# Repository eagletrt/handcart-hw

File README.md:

# Handcart

Battery charger controller board.

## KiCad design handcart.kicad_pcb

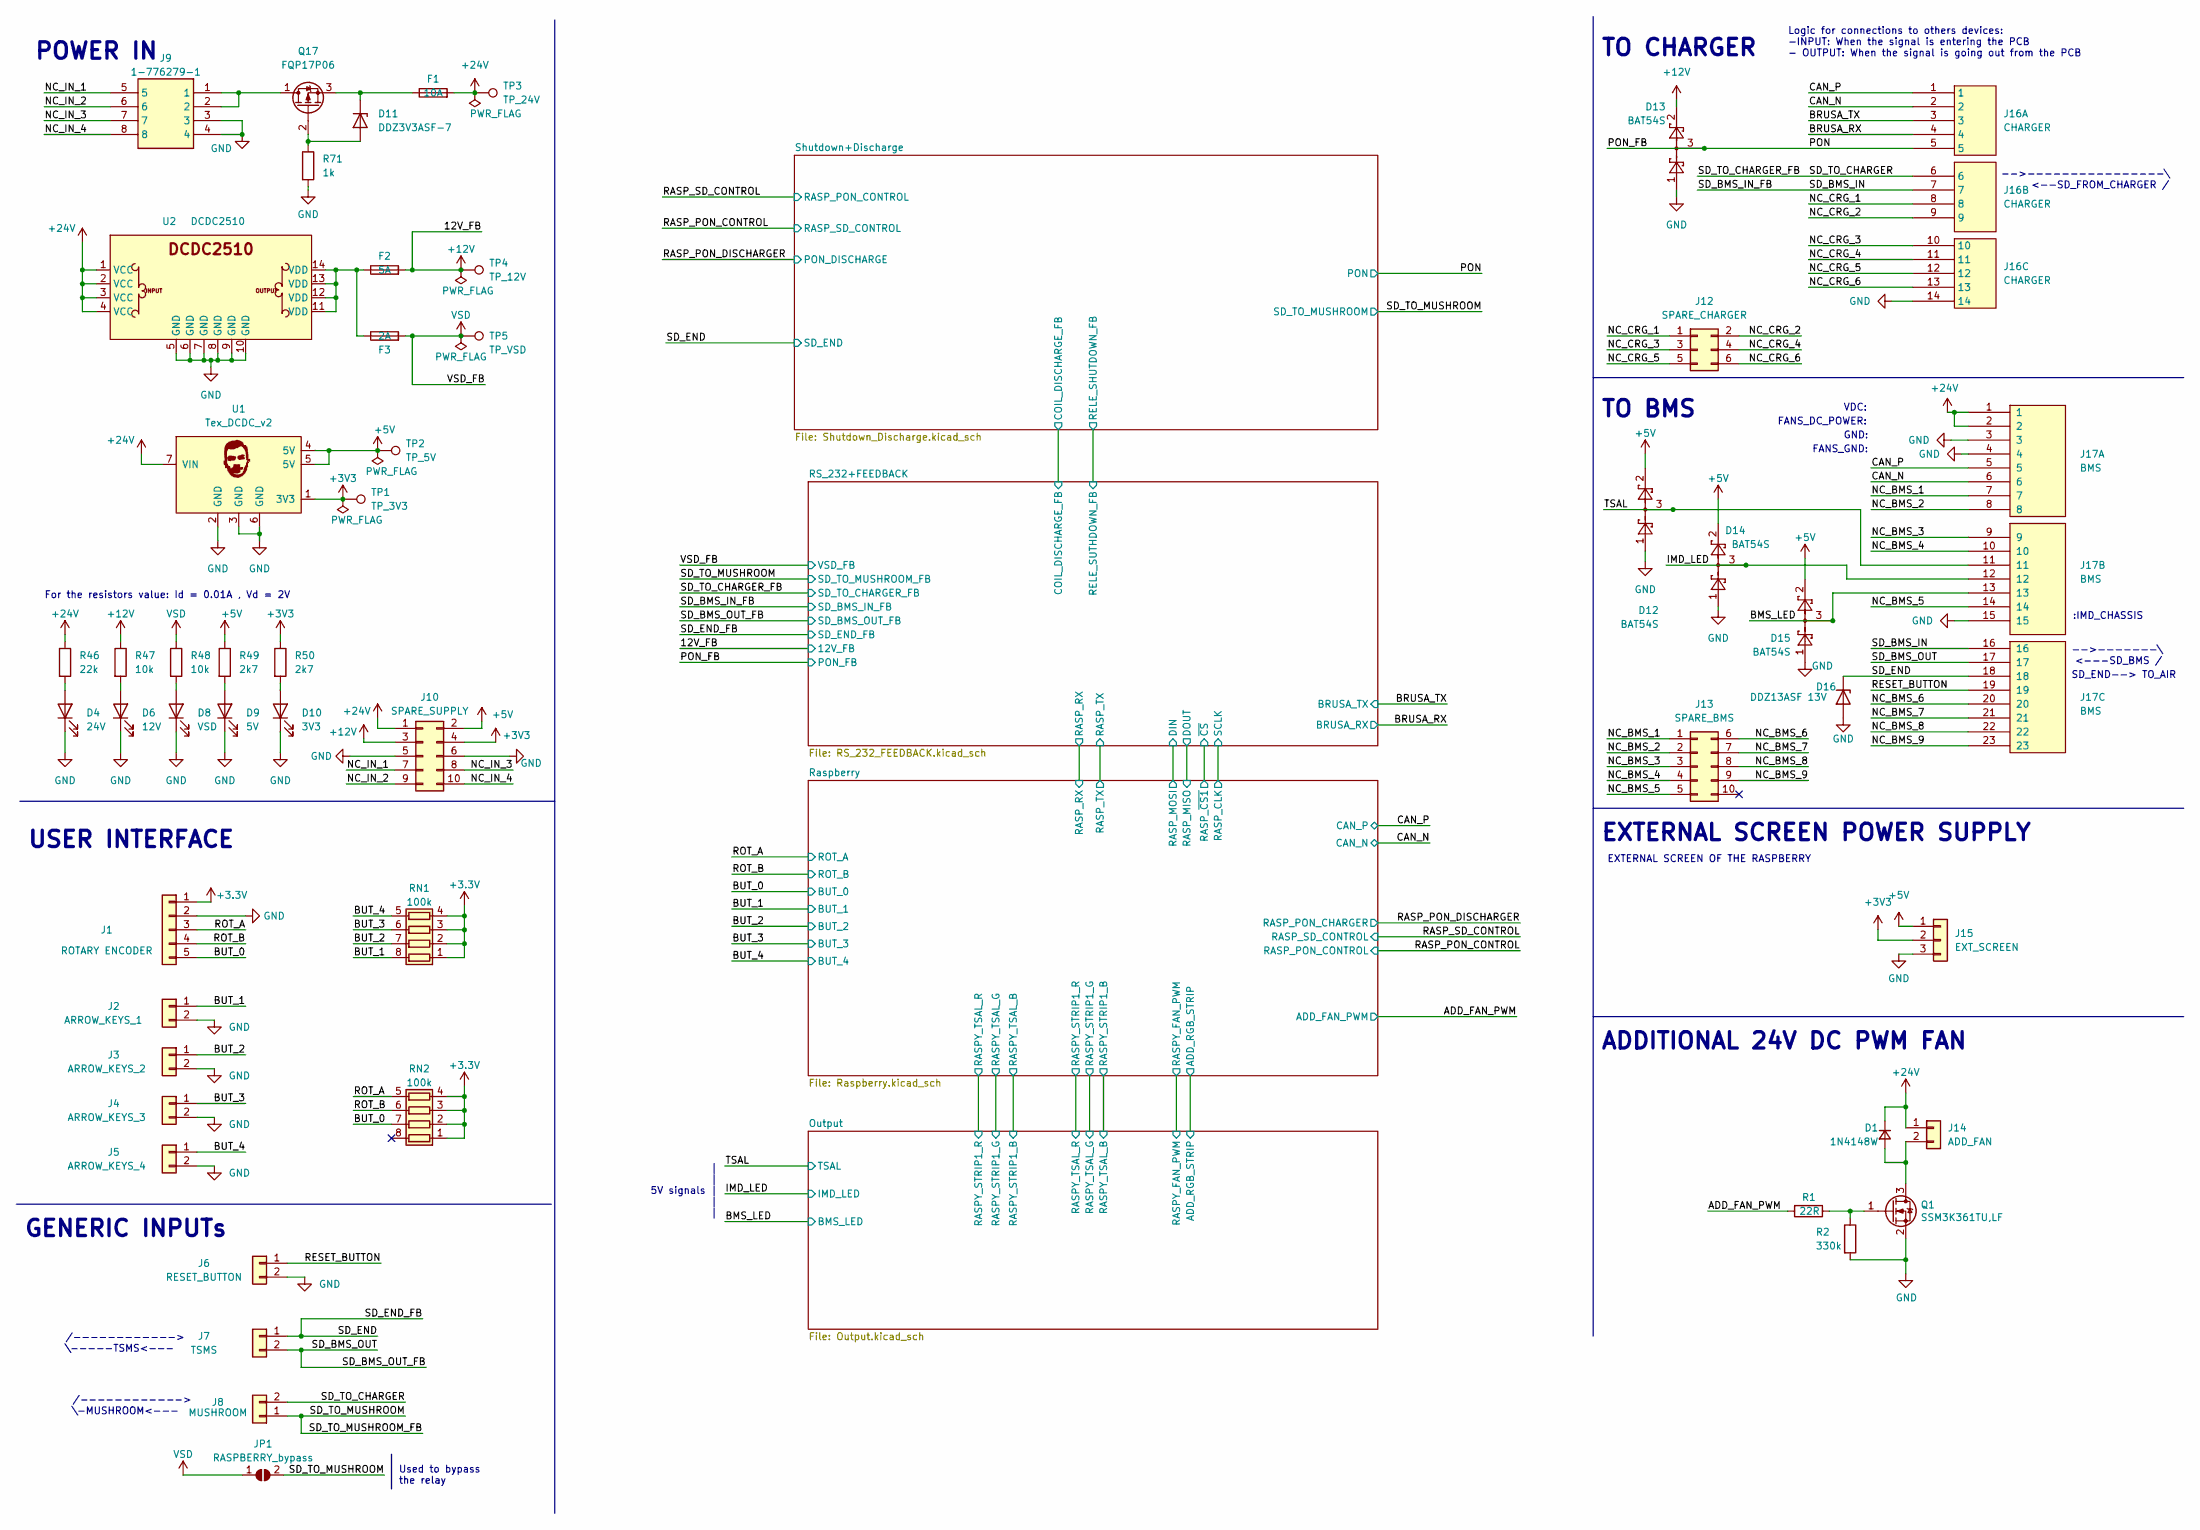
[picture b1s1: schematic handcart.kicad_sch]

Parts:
D1: 1N4148W; D_SOD-323_HandSoldering
D4: 24V; R_0805_2012Metric
D6: 12V; R_0805_2012Metric
D8: VSD; R_0805_2012Metric
D9: 5V; R_0805_2012Metric
D10: 3V3; R_0805_2012Metric
D11: DDZ3V3ASF-7; D_SOD-323
D12, D13, D14, D15: BAT54S; SOT-23
D16: DDZ13ASF 13V; D_SOD-323F
F1: 10A; Keystone-Fuseholder 3557-2
F2: 5A; Keystone-Fuseholder 3557-2
F3: 2A; Keystone-Fuseholder 3557-2
J1: ROTARY ENCODER; Molex_Micro-Fit_3.0_43650-0515_1x05_P3.00mm_Vertical
J2: ARROW_KEYS_1; Molex_Micro-Fit_3.0_43650-0215_1x02_P3.00mm_Vertical
J3: ARROW_KEYS_2; Molex_Micro-Fit_3.0_43650-0215_1x02_P3.00mm_Vertical
J4: ARROW_KEYS_3; Molex_Micro-Fit_3.0_43650-0215_1x02_P3.00mm_Vertical
J5: ARROW_KEYS_4; Molex_Micro-Fit_3.0_43650-0215_1x02_P3.00mm_Vertical
J6: RESET_BUTTON; Molex_Micro-Fit_3.0_43650-0215_1x02_P3.00mm_Vertical
J7: TSMS; Molex_Micro-Fit_3.0_43650-0215_1x02_P3.00mm_Vertical
J8: MUSHROOM; Molex_Micro-Fit_3.0_43650-0215_1x02_P3.00mm_Vertical
J9: 1-776279-1; 17762791; Mouser Part Number 571-1-776279-1
J10: SPARE_SUPPLY; Molex_Micro-Fit_3.0_43045-1012_2x05_P3.00mm_Vertical
J12: SPARE_CHARGER; Molex_Micro-Fit_3.0_43045-0612_2x03_P3.00mm_Vertical
J13: SPARE_BMS; Molex_Micro-Fit_3.0_43045-1012_2x05_P3.00mm_Vertical
J14: ADD_FAN; Molex_Micro-Fit_3.0_43650-0215_1x02_P3.00mm_Vertical
J15: EXT_SCREEN; Molex_Micro-Fit_3.0_43650-0315_1x03_P3.00mm_Vertical
J16: CHARGER; TE_776266-4
J17: BMS; TE_776087-4
JP1: RASPBERRY_bypass; SolderJumper-2_P1.3mm_Open_Pad1.0x1.5mm
Q1: SSM3K361TU,LF; SOTFL65P210X75-3N
Q17: FQP17P06; TO-220-3_Vertical
R1: 22R; R_0603_1608Metric
R2: 330k; R_0603_1608Metric
R46: 22k; R_0603_1608Metric
R47, R48: 10k; R_0603_1608Metric
R49, R50: 2k7; R_0603_1608Metric
R71: 1k; R_0603_1608Metric
RN1, RN2: 100k; R_Array_Convex_4x0603
TP1: TP_3V3; TestPoint_Pad_D2.0mm
TP2: TP_5V; TestPoint_Pad_D2.0mm
TP3: TP_24V; TestPoint_Pad_D2.0mm
TP4: TP_12V; TestPoint_Pad_D2.0mm
TP5: TP_VSD; TestPoint_Pad_D2.0mm
U1: Tex_DCDC_v2; Tex_DCDC_v2_horizontal
U2: DCDC2510; DCDC2510_Horizontal

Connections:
+3.3V: J1.1, RN1.1 (R1.1), RN1.2 (R2.1), RN1.3 (R3.1), RN1.4 (R4.1), RN2.1 (R1.1), RN2.2 (R2.1), RN2.3 (R3.1), RN2.4 (R4.1)
+3V3: J10.4, J15.2, R50.1, TP1.1, U1.1 (3V3); also elsewhere on the board
+5V: D12.2, D14.2, D15.2, J10.2, J15.1, R49.1, TP2.1, U1.4 (5V), U1.5 (5V); also elsewhere on the board
+12V: D13.2, F2.2, J10.3, R47.1, TP4.1; also elsewhere on the board
+24V: D1.1 (K), F1.2, J10.1, J14.1, J17.1, J17.2, R46.1, TP3.1, U1.7 (VIN), U2.1 (VCC), U2.2 (VCC), U2.3 (VCC), U2.4 (VCC); also elsewhere on the board
/ADD_FAN_PWM: R1.2; also elsewhere on the board
/BMS_LED: D15.3, J17.13; also elsewhere on the board
/BRUSA_RX: J16.4; also elsewhere on the board
/BRUSA_TX: J16.3; also elsewhere on the board
/BUT_0: J1.5, RN2.7 (R2.2); also elsewhere on the board
/BUT_1: J2.1, RN1.8 (R1.2); also elsewhere on the board
/BUT_2: J3.1, RN1.7 (R2.2); also elsewhere on the board
/BUT_3: J4.1, RN1.6 (R3.2); also elsewhere on the board
/BUT_4: J5.1, RN1.5 (R4.2); also elsewhere on the board
/CAN_N: J16.2, J17.6; also elsewhere on the board
/CAN_P: J16.1, J17.5; also elsewhere on the board
/IMD_LED: D14.3, J17.12; also elsewhere on the board
/NC_BMS_1: J13.1, J17.7
/NC_BMS_2: J13.2, J17.8
/NC_BMS_3: J13.3, J17.9
/NC_BMS_4: J13.4, J17.10
/NC_BMS_5: J13.5, J17.14
/NC_BMS_6: J13.6, J17.20
/NC_BMS_7: J13.7, J17.21
/NC_BMS_8: J13.8, J17.22
/NC_BMS_9: J13.9, J17.23
/NC_CRG_1: J12.1, J16.8
/NC_CRG_2: J12.2, J16.9
/NC_CRG_3: J12.3, J16.10
/NC_CRG_4: J12.4, J16.11
/NC_CRG_5: J12.5, J16.12
/NC_CRG_6: J12.6, J16.13
/NC_IN_1: J9.5, J10.7
/NC_IN_2: J9.6, J10.9
/NC_IN_3: J9.7, J10.8
/NC_IN_4: J9.8, J10.10
/PON: D13.3, J16.5; also elsewhere on the board
/RESET_BUTTON: J6.1, J17.19
/ROT_A: J1.3, RN2.5 (R4.2); also elsewhere on the board
/ROT_B: J1.4, RN2.6 (R3.2); also elsewhere on the board
/SD_BMS_IN: J16.7, J17.16; also elsewhere on the board
/SD_BMS_OUT: J7.2, J17.17; also elsewhere on the board
/SD_END: D16.1 (K), J7.1, J17.18; also elsewhere on the board
/SD_TO_CHARGER: J8.2, J16.6; also elsewhere on the board
/SD_TO_MUSHROOM: J8.1, JP1.2 (B); also elsewhere on the board
/TSAL: D12.3, J17.11; also elsewhere on the board
GND: D4.1 (K), D6.1 (K), D8.1 (K), D9.1 (K), D10.1 (K), D12.1, D13.1, D14.1, D15.1, D16.2 (A), J1.2, J2.2, J3.2, J4.2, J5.2, J6.2, J9.3, J9.4, J10.5, J10.6, J15.3, J16.14, J17.3, J17.4, J17.15, Q1.2 (S), R2.2, R71.2, U1.2 (GND), U1.3 (GND), U1.6 (GND), U2.5 (GND), U2.6 (GND), U2.7 (GND), U2.8 (GND), U2.9 (GND), U2.10 (GND); also elsewhere on the board
unnamed: D1.2 (A), J14.2, Q1.3 (D)
unnamed: D4.2 (A), R46.2
unnamed: D6.2 (A), R47.2
unnamed: D8.2 (A), R48.2
unnamed: D9.2 (A), R49.2
unnamed: D10.2 (A), R50.2
unnamed: D11.1 (K), F1.1, Q17.3 (S)
unnamed: D11.2 (A), Q17.2 (G), R71.1
unnamed: F2.1, F3.1, U2.11 (VDD), U2.12 (VDD), U2.13 (VDD), U2.14 (VDD)
unnamed: J9.1, J9.2, Q17.1 (D)
unnamed: Q1.1 (G), R1.1, R2.1
VCC: F3.2, JP1.1 (A), R48.1, TP5.1; also elsewhere on the board

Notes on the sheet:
-->-------\ <---SD_BMS /
POWER IN
EXTERNAL SCREEN OF THE RASPBERRY
TO BMS
FANS_GND:
TO CHARGER
-->----------------\ <--SD_FROM_CHARGER /
For the resistors value: Id = 0.01A , Vd = 2V
/------------> \-MUSHROOM<---
Used to bypass the relay
GENERIC INPUTs
/------------> \-----TSMS<---
VDC:
FANS_DC_POWER:
ADDITIONAL 24V DC PWM FAN
EXTERNAL SCREEN POWER SUPPLY
Logic for connections to others devices: -INPUT: When the signal is entering the PCB - OUTPUT: When the signal is going out from the PCB
| | 5V signals | | |
SD_END--> TO_AIR
GND:
:IMD_CHASSIS
USER INTERFACE

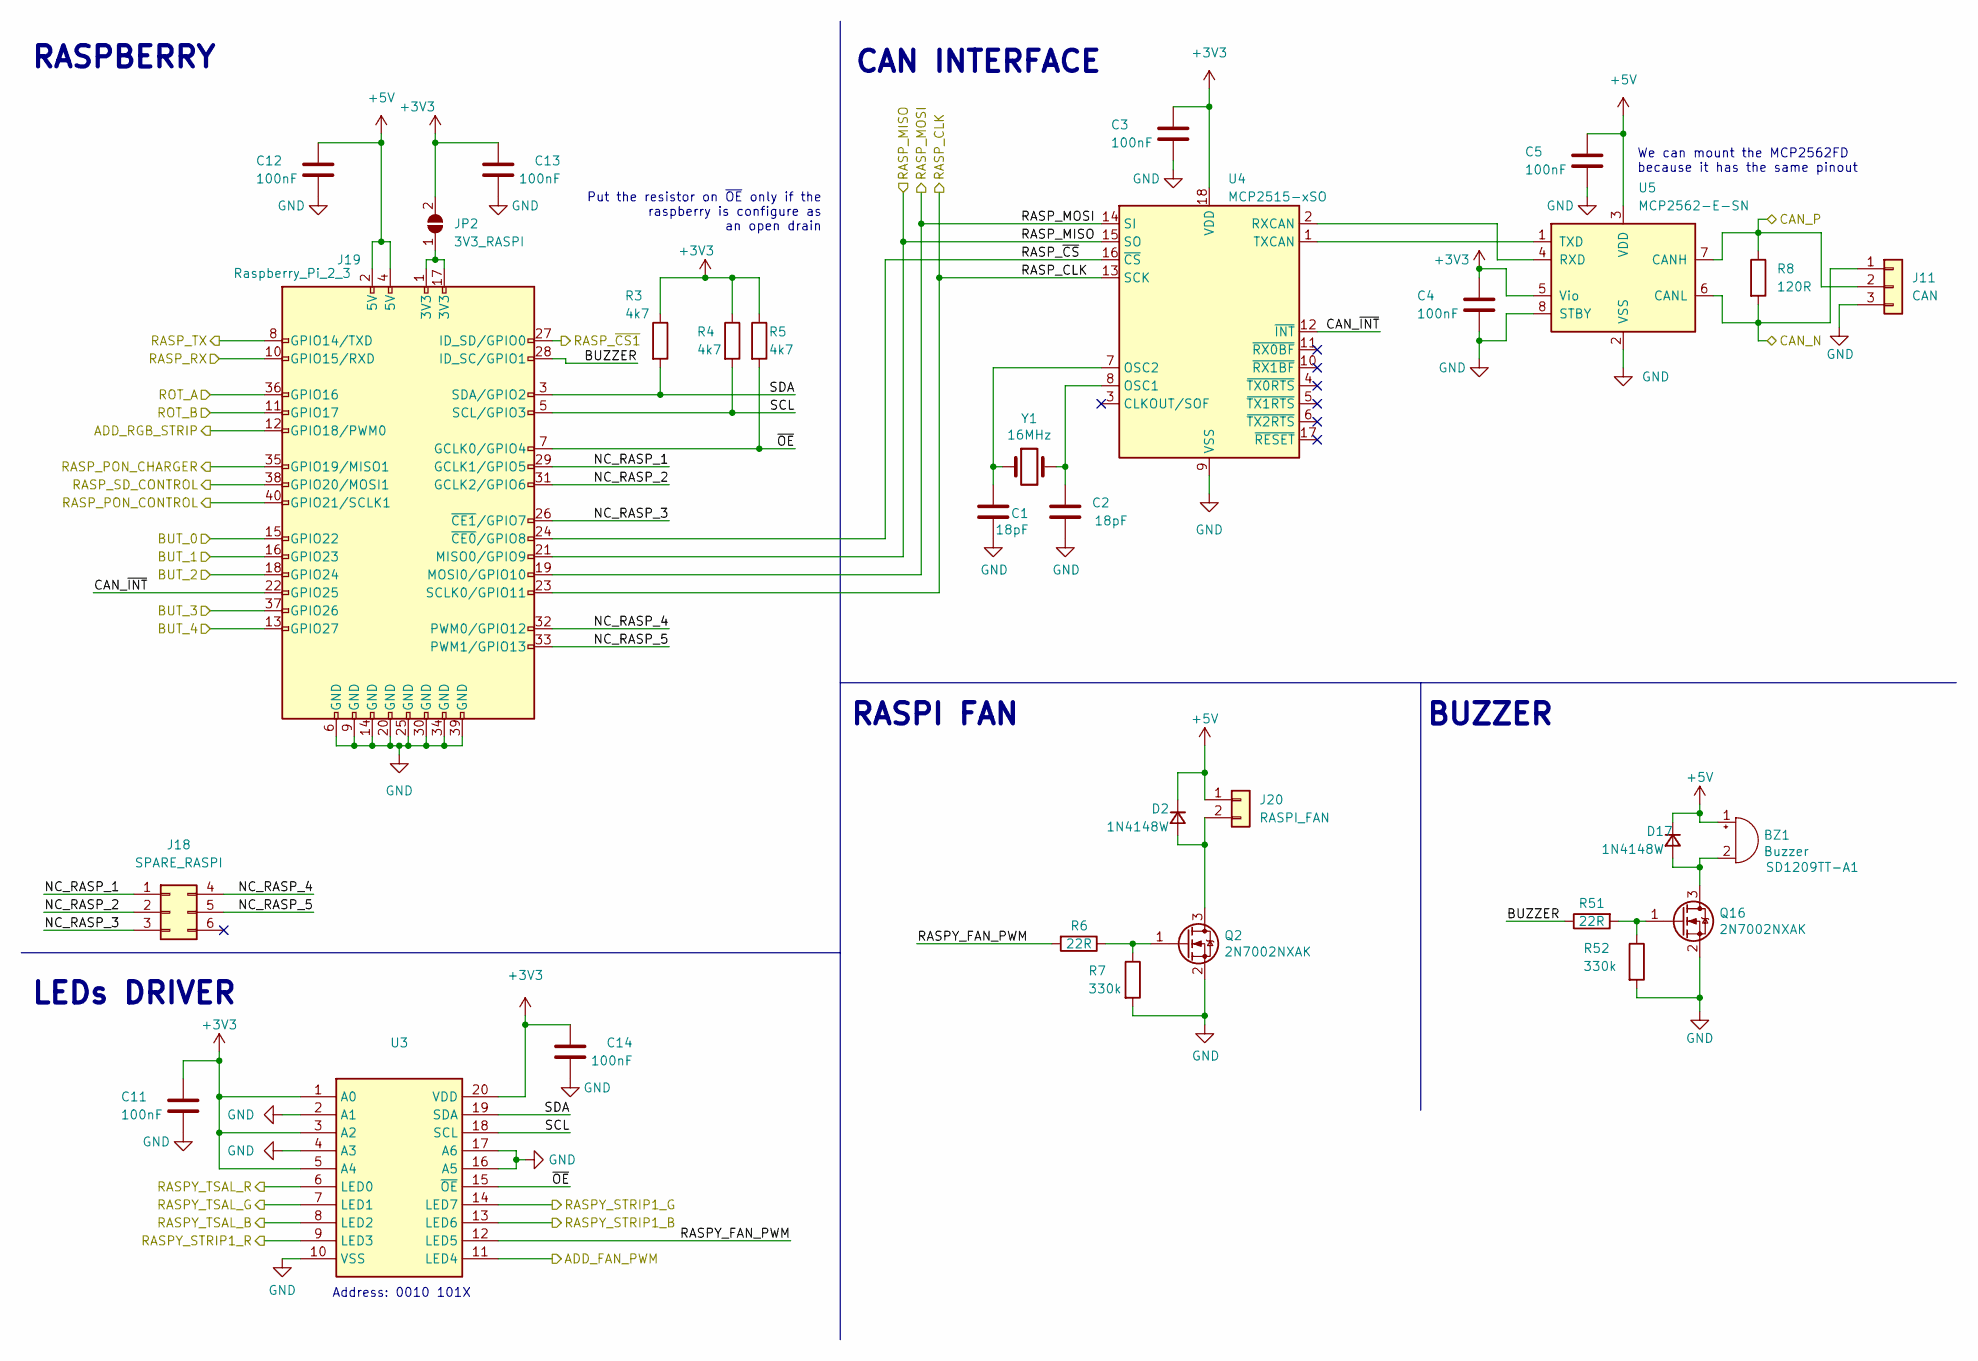
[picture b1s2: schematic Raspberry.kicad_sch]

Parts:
BZ1: Buzzer; Buzzer_TDK_PS1240P02BT_D12.2mm_H6.5mm
C1, C2: 18pF; R_0603_1608Metric
C3, C4, C5, C11, C12, C13, C14: 100nF; R_0805_2012Metric
D2, D17: 1N4148W; D_SOD-323_HandSoldering
J11: CAN; Molex_Micro-Fit_3.0_43650-0315_1x03_P3.00mm_Vertical
J18: SPARE_RASPI; Molex_Micro-Fit_3.0_43045-0612_2x03_P3.00mm_Vertical
J19: Raspberry_Pi_2_3; raspberrypi_hat_template
J20: RASPI_FAN; Molex_Micro-Fit_3.0_43650-0215_1x02_P3.00mm_Vertical
JP2: 3V3_RASPI; SolderJumper-2_P1.3mm_Open_RoundedPad1.0x1.5mm
Q2, Q16: 2N7002NXAK; SOT-23
R3, R4, R5: 4k7; R_0603_1608Metric
R6, R51: 22R; R_0603_1608Metric
R7, R52: 330k; R_0603_1608Metric
R8: 120R; R_0603_1608Metric
U3: PCA9634PW,118; SOP65P640X110-20N; Mouser Part Number 771-PCA9634PW-T
U4: MCP2515-xSO; SOIC-18W_7.5x11.6mm_P1.27mm
U5: MCP2562-E-SN; SOIC-8_3.9x4.9mm_P1.27mm
Y1: 16MHz; Crystal_HC49-4H_Vertical

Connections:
+3V3: C3.1, C4.1, C11.1, C13.1, C14.1, JP2.2 (B), R3.1, R4.1, R5.1, U3.1 (A0), U3.3 (A2), U3.5 (A4), U3.20 (VDD), U4.18 (VDD), U5.5 (Vio); also elsewhere on the board
+5V: BZ1.1 (-), C5.1, C12.1, D2.1 (K), D17.1 (K), J19.2 (5V), J19.4 (5V), J20.1, U5.3 (VDD); also elsewhere on the board
/ADD_FAN_PWM: U3.11 (LED4); also elsewhere on the board
/BUT_0: J19.15 (GPIO22); also elsewhere on the board
/BUT_1: J19.16 (GPIO23); also elsewhere on the board
/BUT_2: J19.18 (GPIO24); also elsewhere on the board
/BUT_3: J19.37 (GPIO26); also elsewhere on the board
/BUT_4: J19.13 (GPIO27); also elsewhere on the board
/CAN_N: J11.1, R8.2, U5.6 (CANL); also elsewhere on the board
/CAN_P: J11.2, R8.1, U5.7 (CANH); also elsewhere on the board
/Output/ADD_RGB_STRIP: J19.12 (GPIO18/PWM0); also elsewhere on the board
/Output/RASPY_STRIP1_B: U3.8 (LED2); also elsewhere on the board
/Output/RASPY_STRIP1_G: U3.7 (LED1); also elsewhere on the board
/Output/RASPY_STRIP1_R: U3.6 (LED0); also elsewhere on the board
/Output/RASPY_TSAL_B: U3.13 (LED6); also elsewhere on the board
/Output/RASPY_TSAL_G: U3.14 (LED7); also elsewhere on the board
/Output/RASPY_TSAL_R: U3.9 (LED3); also elsewhere on the board
/RASP_PON_CONTROL: J19.40 (GPIO21/SCLK1); also elsewhere on the board
/RASP_PON_DISCHARGER: J19.35 (GPIO19/MISO1); also elsewhere on the board
/RASP_SD_CONTROL: J19.38 (GPIO20/MOSI1); also elsewhere on the board
/ROT_A: J19.36 (GPIO16); also elsewhere on the board
/ROT_B: J19.11 (GPIO17); also elsewhere on the board
/RS_232+FEEDBACK/RASP_RX: J19.10 (GPIO15/RXD); also elsewhere on the board
/RS_232+FEEDBACK/RASP_TX: J19.8 (GPIO14/TXD); also elsewhere on the board
/RS_232+FEEDBACK/~CS: J19.27 (ID_SD/GPIO0); also elsewhere on the board
/Raspberry/BUZZER: J19.28 (ID_SC/GPIO1), R51.1
/Raspberry/CAN_~INT: J19.22 (GPIO25), U4.12 (~INT)
/Raspberry/NC_RASP_1: J18.1, J19.29 (GCLK1/GPIO5)
/Raspberry/NC_RASP_2: J18.2, J19.31 (GCLK2/GPIO6)
/Raspberry/NC_RASP_3: J18.3, J19.26 (~CE1/GPIO7)
/Raspberry/NC_RASP_4: J18.4, J19.32 (PWM0/GPIO12)
/Raspberry/NC_RASP_5: J18.5, J19.33 (PWM1/GPIO13)
/Raspberry/RASPY_FAN_PWM: R6.2, U3.12 (LED5)
/Raspberry/RASP_CLK: J19.23 (SCLK0/GPIO11), U4.13 (SCK); also elsewhere on the board
/Raspberry/RASP_MISO: J19.21 (MISO0/GPIO9), U4.15 (SO); also elsewhere on the board
/Raspberry/RASP_MOSI: J19.19 (MOSI0/GPIO10), U4.14 (SI); also elsewhere on the board
/Raspberry/RASP_~CS: J19.24 (~CE0/GPIO8), U4.16 (~CS)
/Raspberry/SCL: J19.5 (SCL/GPIO3), R4.2, U3.18 (SCL)
/Raspberry/SDA: J19.3 (SDA/GPIO2), R3.2, U3.19 (SDA)
/Raspberry/~OE: J19.7 (GCLK0/GPIO4), R5.2, U3.15 (~OE)
GND: C1.2, C2.2, C3.2, C4.2, C5.2, C11.2, C12.2, C13.2, C14.2, J11.3, J19.6 (GND), J19.9 (GND), J19.14 (GND), J19.20 (GND), J19.25 (GND), J19.30 (GND), J19.34 (GND), J19.39 (GND), Q2.2 (S), Q16.2 (S), R7.2, R52.2, U3.2 (A1), U3.4 (A3), U3.10 (VSS), U3.16 (A5), U3.17 (A6), U4.9 (VSS), U5.2 (VSS), U5.8 (STBY); also elsewhere on the board
unnamed: BZ1.2 (+), D17.2 (A), Q16.3 (D)
unnamed: C1.1, U4.7 (OSC2), Y1.1
unnamed: C2.1, U4.8 (OSC1), Y1.2
unnamed: D2.2 (A), J20.2, Q2.3 (D)
unnamed: J19.1 (3V3), J19.17 (3V3), JP2.1 (A)
unnamed: Q2.1 (G), R6.1, R7.1
unnamed: Q16.1 (G), R51.2, R52.1
unnamed: U4.1 (TXCAN), U5.1 (TXD)
unnamed: U4.2 (RXCAN), U5.4 (RXD)

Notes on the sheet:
RASPI FAN
RASPBERRY
BUZZER
Address: 0010 101X
LEDs DRIVER
We can mount the MCP2562FD because it has the same pinout
Put the resistor on ~{OE} only if the raspberry is configure as an open drain
CAN INTERFACE

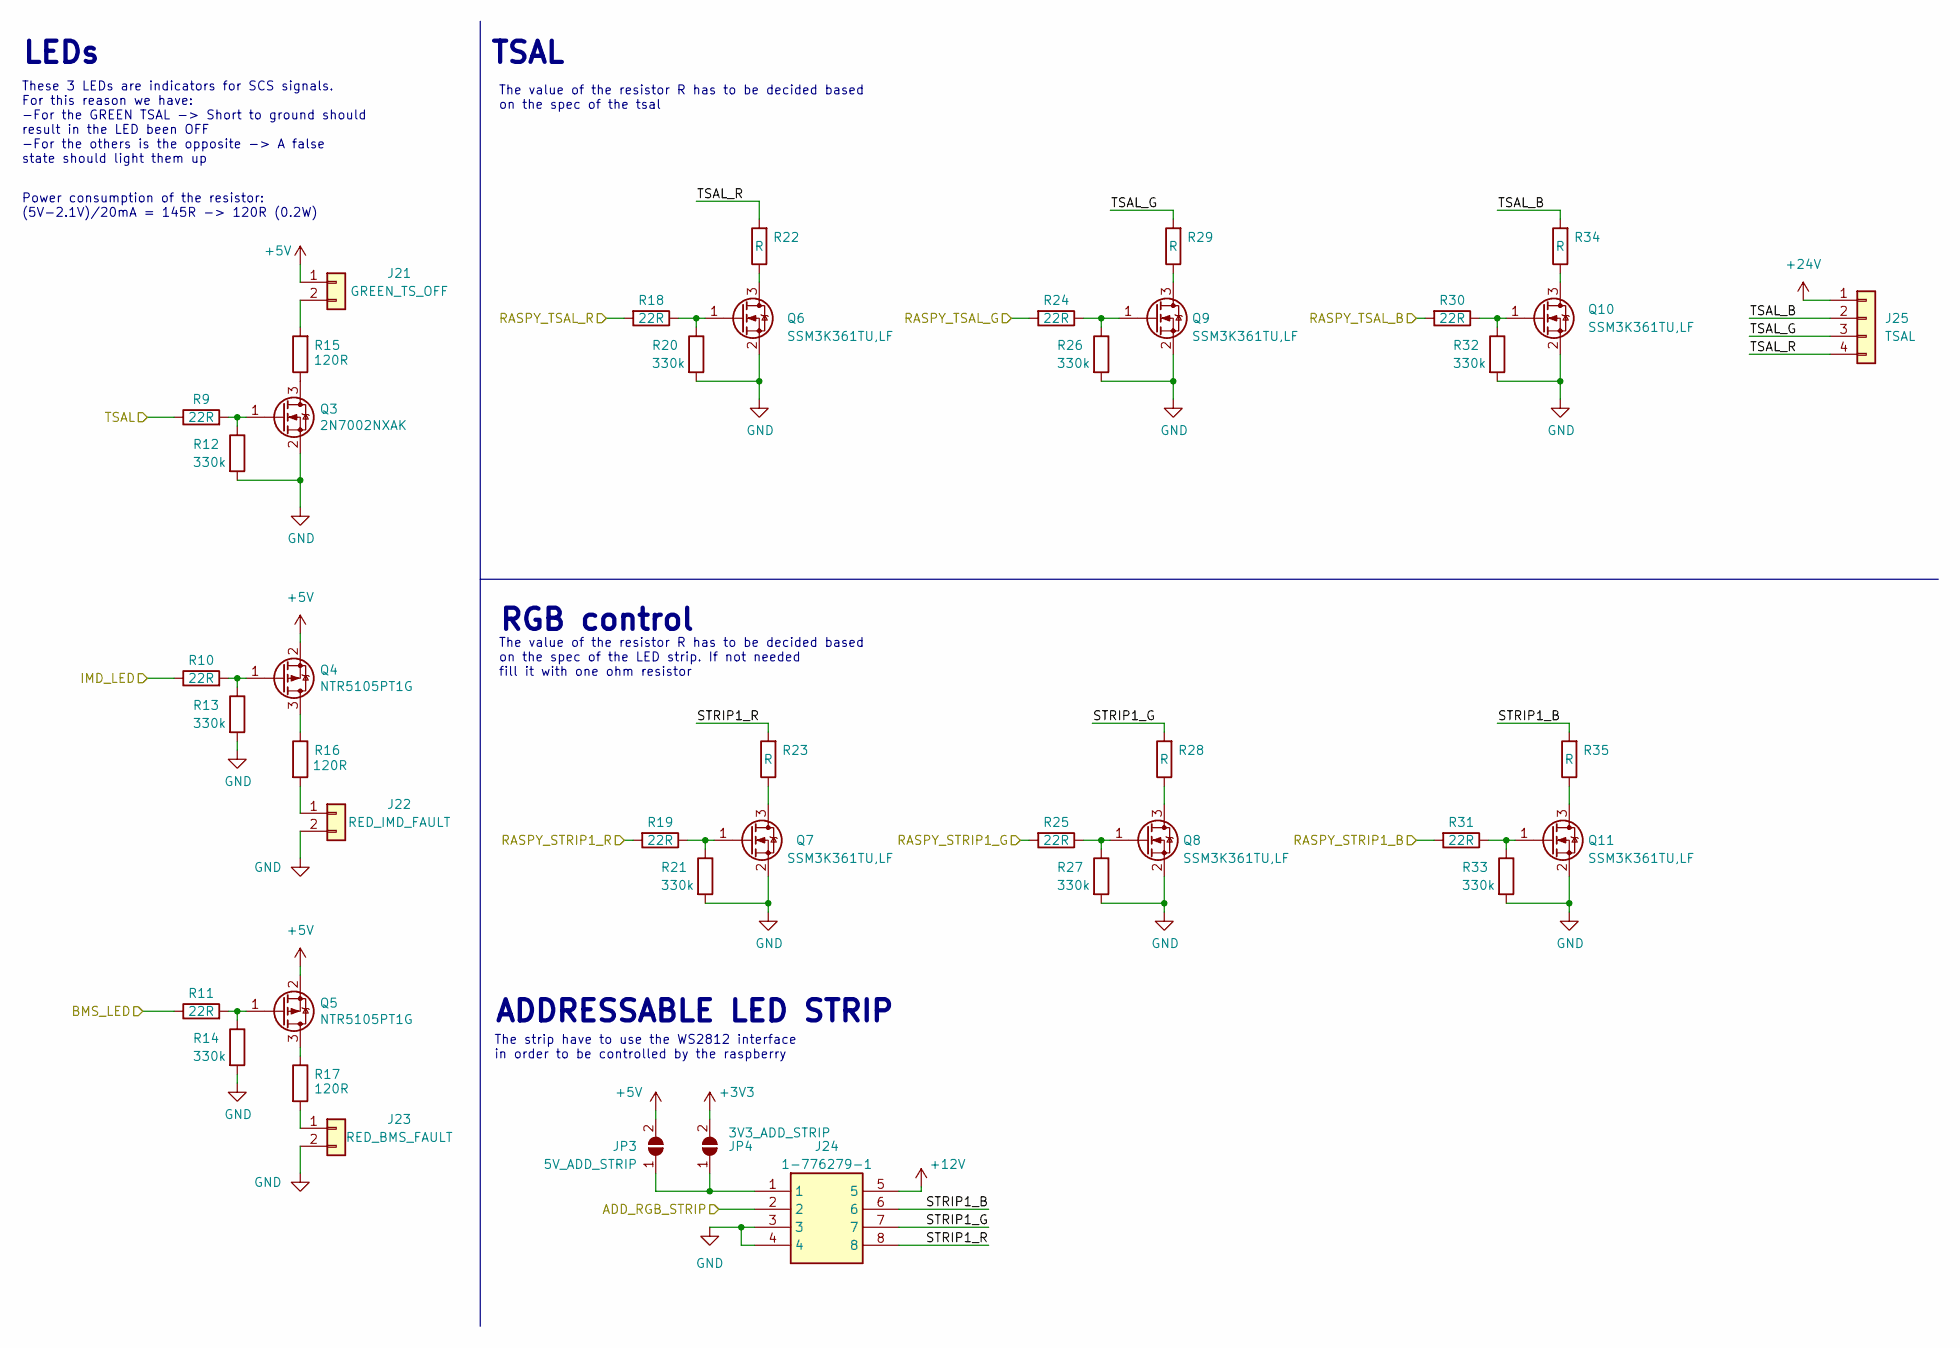
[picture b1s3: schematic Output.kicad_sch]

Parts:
J21: GREEN_TS_OFF; Molex_Micro-Fit_3.0_43650-0215_1x02_P3.00mm_Vertical
J22: RED_IMD_FAULT; Molex_Micro-Fit_3.0_43650-0215_1x02_P3.00mm_Vertical
J23: RED_BMS_FAULT; Molex_Micro-Fit_3.0_43650-0215_1x02_P3.00mm_Vertical
J24: 1-776279-1; 17762791; Mouser Part Number 571-1-776279-1
J25: TSAL; Molex_Micro-Fit_3.0_43650-0415_1x04_P3.00mm_Vertical
JP3: 5V_ADD_STRIP; SolderJumper-2_P1.3mm_Open_RoundedPad1.0x1.5mm
JP4: 3V3_ADD_STRIP; SolderJumper-2_P1.3mm_Open_RoundedPad1.0x1.5mm
Q3: 2N7002NXAK; SOT-23
Q4, Q5: NTR5105PT1G; SOT-23
Q6, Q7, Q8, Q9, Q10, Q11: SSM3K361TU,LF; SOTFL65P210X75-3N; Mouser Part Number 757-SSM3K361TULF
R9, R10, R11, R18, R19, R24, R25, R30, R31: 22R; R_0603_1608Metric
R12, R13, R14, R20, R21, R26, R27, R32, R33: 330k; R_0603_1608Metric
R15, R16, R17: 120R; R_0603_1608Metric
R22, R23, R28, R29, R34, R35: R; R_0805_2012Metric

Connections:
+3V3: JP4.2 (B); also elsewhere on the board
+5V: J21.1, JP3.2 (B), Q4.2 (S), Q5.2 (S); also elsewhere on the board
+12V: J24.5; also elsewhere on the board
+24V: J25.1; also elsewhere on the board
/BMS_LED: R11.1; also elsewhere on the board
/IMD_LED: R10.1; also elsewhere on the board
/Output/ADD_RGB_STRIP: J24.2; also elsewhere on the board
/Output/RASPY_STRIP1_B: R31.2; also elsewhere on the board
/Output/RASPY_STRIP1_G: R25.2; also elsewhere on the board
/Output/RASPY_STRIP1_R: R19.2; also elsewhere on the board
/Output/RASPY_TSAL_B: R30.2; also elsewhere on the board
/Output/RASPY_TSAL_G: R24.2; also elsewhere on the board
/Output/RASPY_TSAL_R: R18.2; also elsewhere on the board
/Output/STRIP1_B: J24.6, R35.2
/Output/STRIP1_G: J24.7, R28.2
/Output/STRIP1_R: J24.8, R23.2
/Output/TSAL_B: J25.2, R34.2
/Output/TSAL_G: J25.3, R29.2
/Output/TSAL_R: J25.4, R22.2
/TSAL: R9.1; also elsewhere on the board
GND: J22.2, J23.2, J24.3, J24.4, Q3.2 (S), Q6.2 (S), Q7.2 (S), Q8.2 (S), Q9.2 (S), Q10.2 (S), Q11.2 (S), R12.2, R13.2, R14.2, R20.2, R21.2, R26.2, R27.2, R32.2, R33.2; also elsewhere on the board
unnamed: J21.2, R15.2
unnamed: J22.1, R16.2
unnamed: J23.1, R17.2
unnamed: J24.1, JP3.1 (A), JP4.1 (A)
unnamed: Q3.1 (G), R9.2, R12.1
unnamed: Q3.3 (D), R15.1
unnamed: Q4.1 (G), R10.2, R13.1
unnamed: Q4.3 (D), R16.1
unnamed: Q5.1 (G), R11.2, R14.1
unnamed: Q5.3 (D), R17.1
unnamed: Q6.1 (G), R18.1, R20.1
unnamed: Q6.3 (D), R22.1
unnamed: Q7.1 (G), R19.1, R21.1
unnamed: Q7.3 (D), R23.1
unnamed: Q8.1 (G), R25.1, R27.1
unnamed: Q8.3 (D), R28.1
unnamed: Q9.1 (G), R24.1, R26.1
unnamed: Q9.3 (D), R29.1
unnamed: Q10.1 (G), R30.1, R32.1
unnamed: Q10.3 (D), R34.1
unnamed: Q11.1 (G), R31.1, R33.1
unnamed: Q11.3 (D), R35.1

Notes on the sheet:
ADDRESSABLE LED STRIP
These 3 LEDs are indicators for SCS signals. For this reason we have: -For the GREEN TSAL -> Short to ground should result in the LED been OFF -For the others is the opposite -> A false state should light them up
RGB control
LEDs
TSAL
Power consumption of the resistor: (5V-2.1V)/20mA = 145R -> 120R (0.2W)
The value of the resistor R has to be decided based on the spec of the LED strip. If not needed fill it with one ohm resistor
The value of the resistor R has to be decided based on the spec of the tsal
The strip have to use the WS2812 interface in order to be controlled by the raspberry

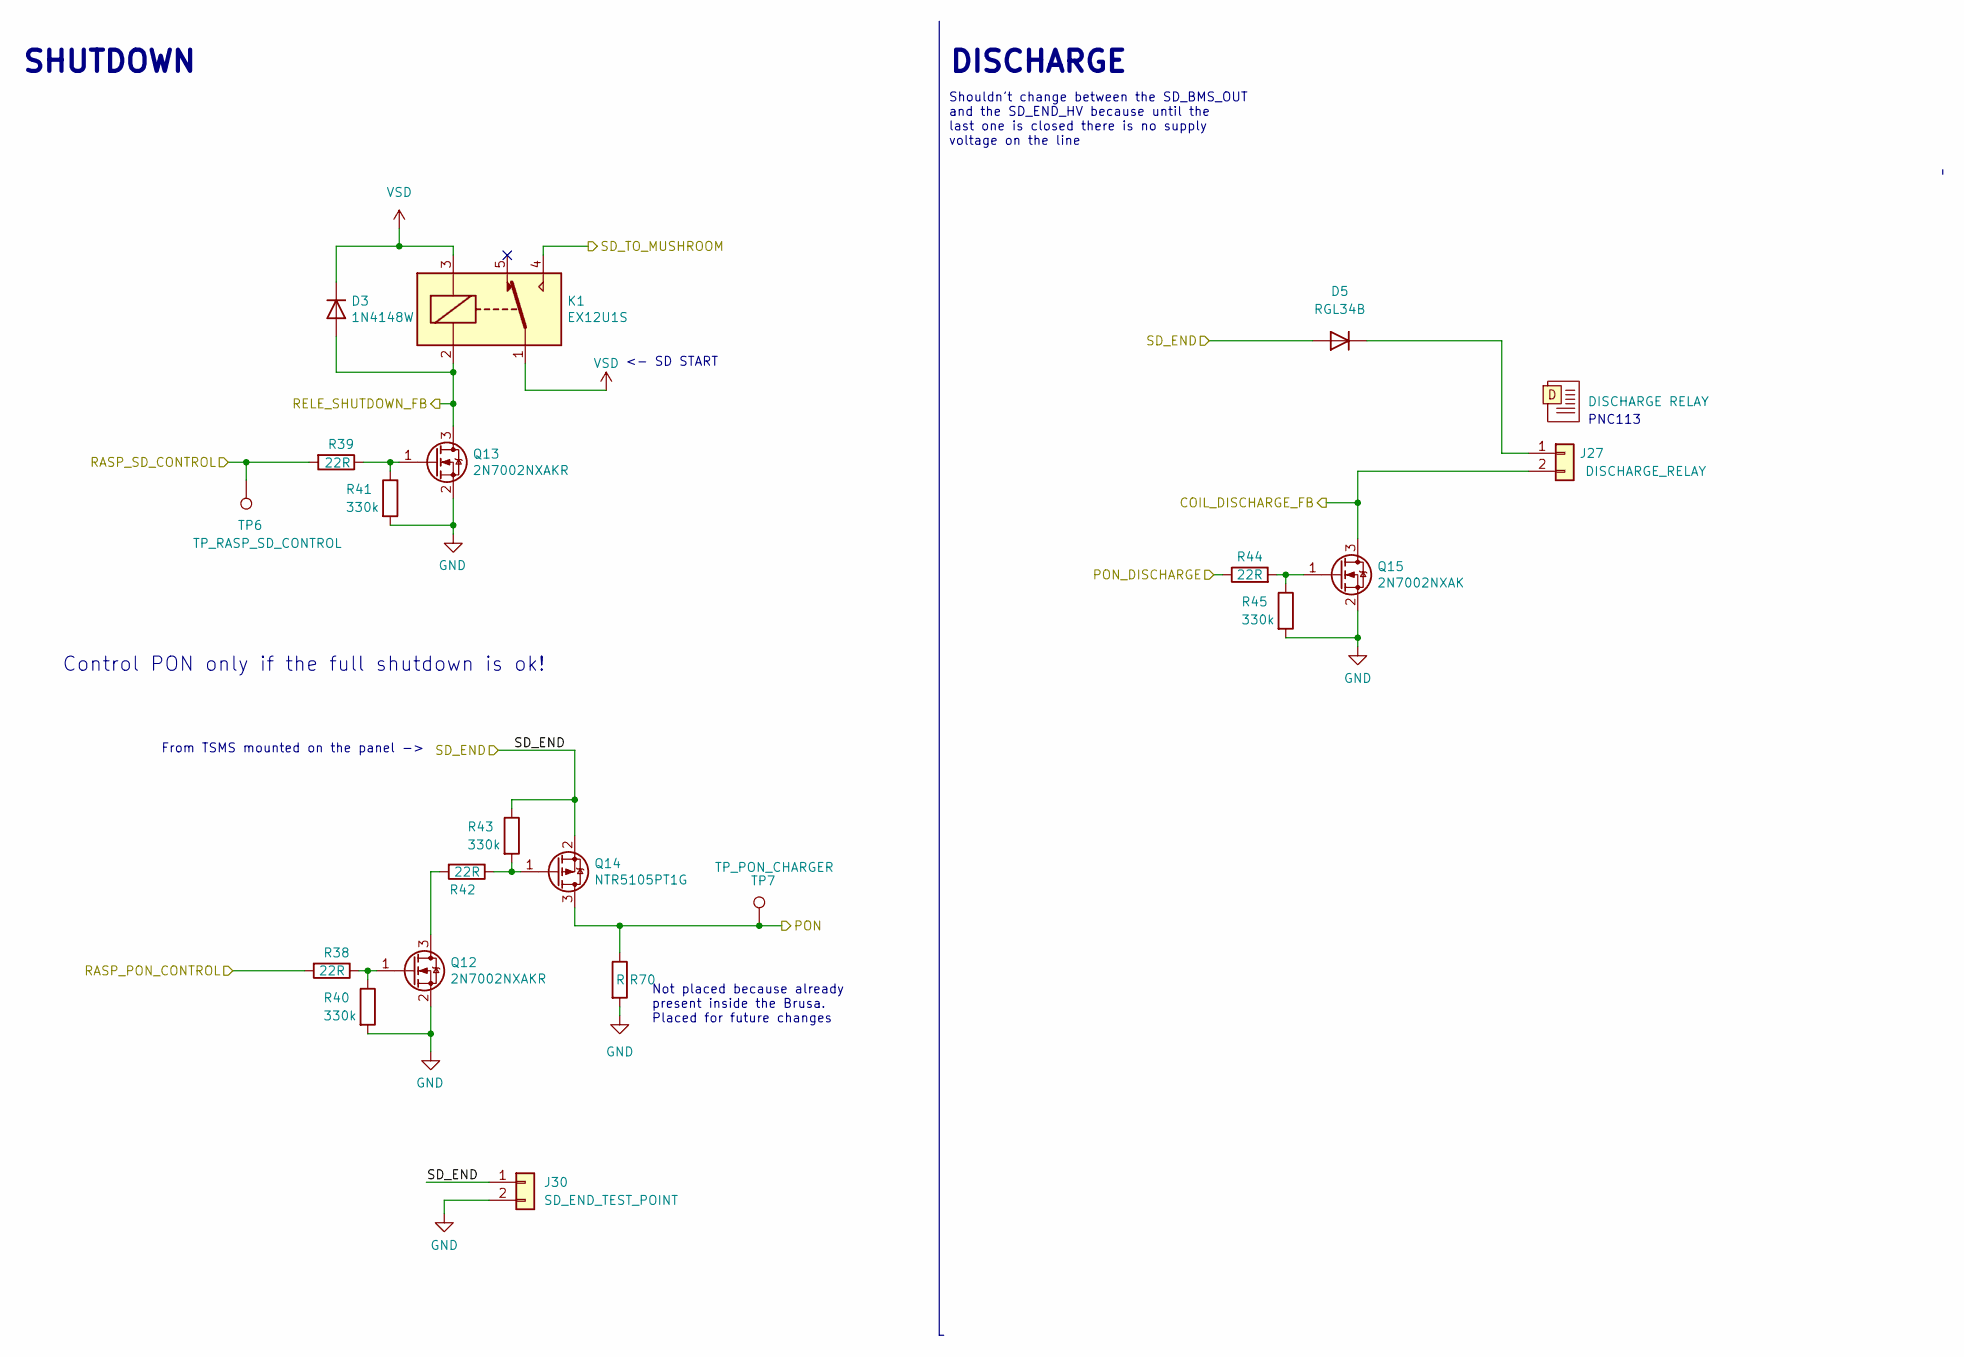
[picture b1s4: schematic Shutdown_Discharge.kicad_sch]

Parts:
D3: 1N4148W; D_SOD-123
D5: RGL34B; D_MiniMELF
D7: DISCHARGE RELAY
J27: DISCHARGE_RELAY; Molex_Micro-Fit_3.0_43650-0215_1x02_P3.00mm_Vertical
J30: SD_END_TEST_POINT; Molex_Micro-Fit_3.0_43650-0215_1x02_P3.00mm_Vertical
K1: EX12U1S
Q12, Q13: 2N7002NXAKR; SOT-23
Q14: NTR5105PT1G; SOT-23
Q15: 2N7002NXAK; SOT-23
R38, R39, R42, R44: 22R; R_0603_1608Metric
R40, R41, R43, R45: 330k; R_0603_1608Metric
R70: R; R_0805_2012Metric
TP6: TP_RASP_SD_CONTROL; TestPoint_Pad_D2.0mm
TP7: TP_PON_CHARGER; TestPoint_Pad_D2.0mm

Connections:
/PON: Q14.3 (D), R70.1, TP7.1; also elsewhere on the board
/RASP_PON_CONTROL: R39.2, TP6.1; also elsewhere on the board
/RASP_PON_DISCHARGER: R44.1; also elsewhere on the board
/RASP_SD_CONTROL: R38.2; also elsewhere on the board
/RS_232+FEEDBACK/COIL_DISCHARGE_FB: J27.2, Q15.3 (D); also elsewhere on the board
/RS_232+FEEDBACK/RELE_SUTHDOWN_FB: D3.2 (A), K1.2, Q13.3 (D); also elsewhere on the board
/SD_END: D5.2 (A), J30.1, Q14.2 (S), R43.1; also elsewhere on the board
/SD_TO_MUSHROOM: K1.4; also elsewhere on the board
GND: J30.2, Q12.2 (S), Q13.2 (S), Q15.2 (S), R40.2, R41.2, R45.2, R70.2; also elsewhere on the board
unnamed: D5.1 (K), J27.1
unnamed: Q12.1 (G), R38.1, R40.1
unnamed: Q12.3 (D), R42.2
unnamed: Q13.1 (G), R39.1, R41.1
unnamed: Q14.1 (G), R42.1, R43.2
unnamed: Q15.1 (G), R44.2, R45.1
VCC: D3.1 (K), K1.1, K1.3; also elsewhere on the board

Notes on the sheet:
From TSMS mounted on the panel ->
<- SD START
SHUTDOWN
Shouldn't change between the SD_BMS_OUT and the SD_END_HV because until the last one is closed there is no supply voltage on the line
Not placed because already present inside the Brusa. Placed for future changes
PNC113
DISCHARGE
Control PON only if the full shutdown is ok!
